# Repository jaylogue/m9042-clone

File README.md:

# M9042 Clone

M9042 clone is a PCB clone of the DEC M9042 Unibus module.  It provides an easy to build replacement for the original hardware, which is now hard to come by.

The original M9042 is a Unibus extension card for use in DEC PDP and Vax computers.  The M9042 makes it possible to extend a single Unibus bus across multiple chassis.  M9042s are used in pairs, one in each chassis, and connected via a set of three 40-pin ribbon cables (referred to as H854 cables).  The M9042 itself a short-form, dual height Unibus card which is designed to plug into the A and B connectors in a standard Unibus in/out slot.

The M9042 clone board is a straightforward redesign of the original M9042.  It has the same form-factor as the original and carries all the same Unibus signals and ground lines, in their same connector positions.  It also has a similar (although not identical) trace layout, with significant ground plane coverage, like the original.

* [M9042 clone schematic](docs/m9042-clone-sch.pdf)
* [M9042 clone PCB](docs/m9042-clone-pcb.pdf)

Documentation for the original M9042 (really just the board layout) can be found in the DW720 Field Maintenance Print Set, pp. 151-153 (available on [bitsavers](https://www.google.com/url?sa=t&rct=j&q=&esrc=s&source=web&cd=&cad=rja&uact=8&ved=2ahUKEwjrjoDqwcLzAhX1JTQIHfo5BsIQFnoECAIQAQ&url=http%3A%2F%2Fwww.bitsavers.org%2Fpdf%2Fdec%2Fvax%2F780%2FMP00497_DW780_Dec77.pdf&usg=AOvVaw0sKogK5xX24SyNcEcva4TK)).

The Computer History Wiki also has a useful page on the [H854 header pinout](https://gunkies.org/wiki/UNIBUS_H854_header_pinout).

## Repo Contents

The m9042-clone repo includes the following files:

* `kicad/*` – KiCad 5.x project files containing the schematic and PCB layout
* `pcb-plots/*` – Gerber and drill list files for the m9042-clone PCB
* `docs/*` – Various documentation files

## Parts List

A M9042 clone board is made up of exactly 4 parts: the PCB and three 40-pin latching ribbon cable headers. (Remember, though, that you need two M9042s to form an interconnect).  

I designed the board around the following headers.  These are intended to accommodate IDC ribbon cable connectors **without** strain reliefs.  Other choices (and sources) will likely work as well.

[TE Connectivity 5499913-9 – AMP-LATCH 40 Position Header](https://www.te.com/usa-en/product-5499913-9.html)

Three 40-pin ribbon cables are required to connect the boards together.  These are standard straight-through ribbon cables with 40-pin IDC connectors.  For ease of fitting the cables, its best if the cable exits the connector on the side with the registration tab.

## Ordering PCBs

The `pcb-plots` directory contains all the files necessary to order PCBs from a prototype PCB house such as [JLCPCB](https://jlcpcb.com/).

When ordering PCBs, be sure to request the following options:

* ENIG or hard gold surface finish
* Beveled connector edges
* Board thickness 1.4mm to 1.6mm

Board thicknesses of 1.6mm are common.  DEC specified its boards to be .056" (+/-0.005) thick, which makes 1.6mm a little big.  In practice, though, it does work.

Technically, a hard gold surface finish is best to ensure durability of the edge connectors against repeated insertions/removals.  Unfortunately it is expensive and not offered by many PCB manufactures.  ENIG is a more affordable compromise.

## M9042 Pin Numbering and Cable Orientation

One slight difference between the original M9042 and the clone is the numbering scheme used for the ribbon cable connectors.  Modern ribbon cable connectors place pin #1 in the upper right when looking into the connector pins with the registration slot facing up.  (A little arrow on the header marks the location of pin #1).  This orientation results in the red stripe on a ribbon cable being towards the right of the header when connected.

Historically, however, DEC considered the first pin (pin A) to be the one on the lower left of the connector, with numbering going in the opposite direction.  **In practice, this difference is of no consequence**, because all connections between pairs of M9042s are straight-though, and the registration tabs prevents connectors from being inserted upside-down.

Do however make sure to properly interconnect the three cables between their respective headers on each M9042 (J1-to-J1, J2-to-J2, etc.), as mixing these up would almost certainly be bad.

## WARNING

The M9042 clone has been successfully tested as an interconnect between a PDP-11/05 and an ME11-L box. _**This, however, is the extent of the testing done to date**_ (because that's all the hardware I have).

Because of this, anyone attempting to use the M9042 clone in their own equipment should proceed with caution, as I make no guarantee that it won't cause damage to your precious retro equipment.

If it does end up working for you, please drop me a line and let me know.

## License

The M9042 clone project, including the schematics, PCB layouts, all associated documentation and this README, are licensed under a [Creative Commons Attribution 4.0 International License](https://creativecommons.org/licenses/by/4.0/).  The file `LICENSE.TXT` contains a copy these provisions.

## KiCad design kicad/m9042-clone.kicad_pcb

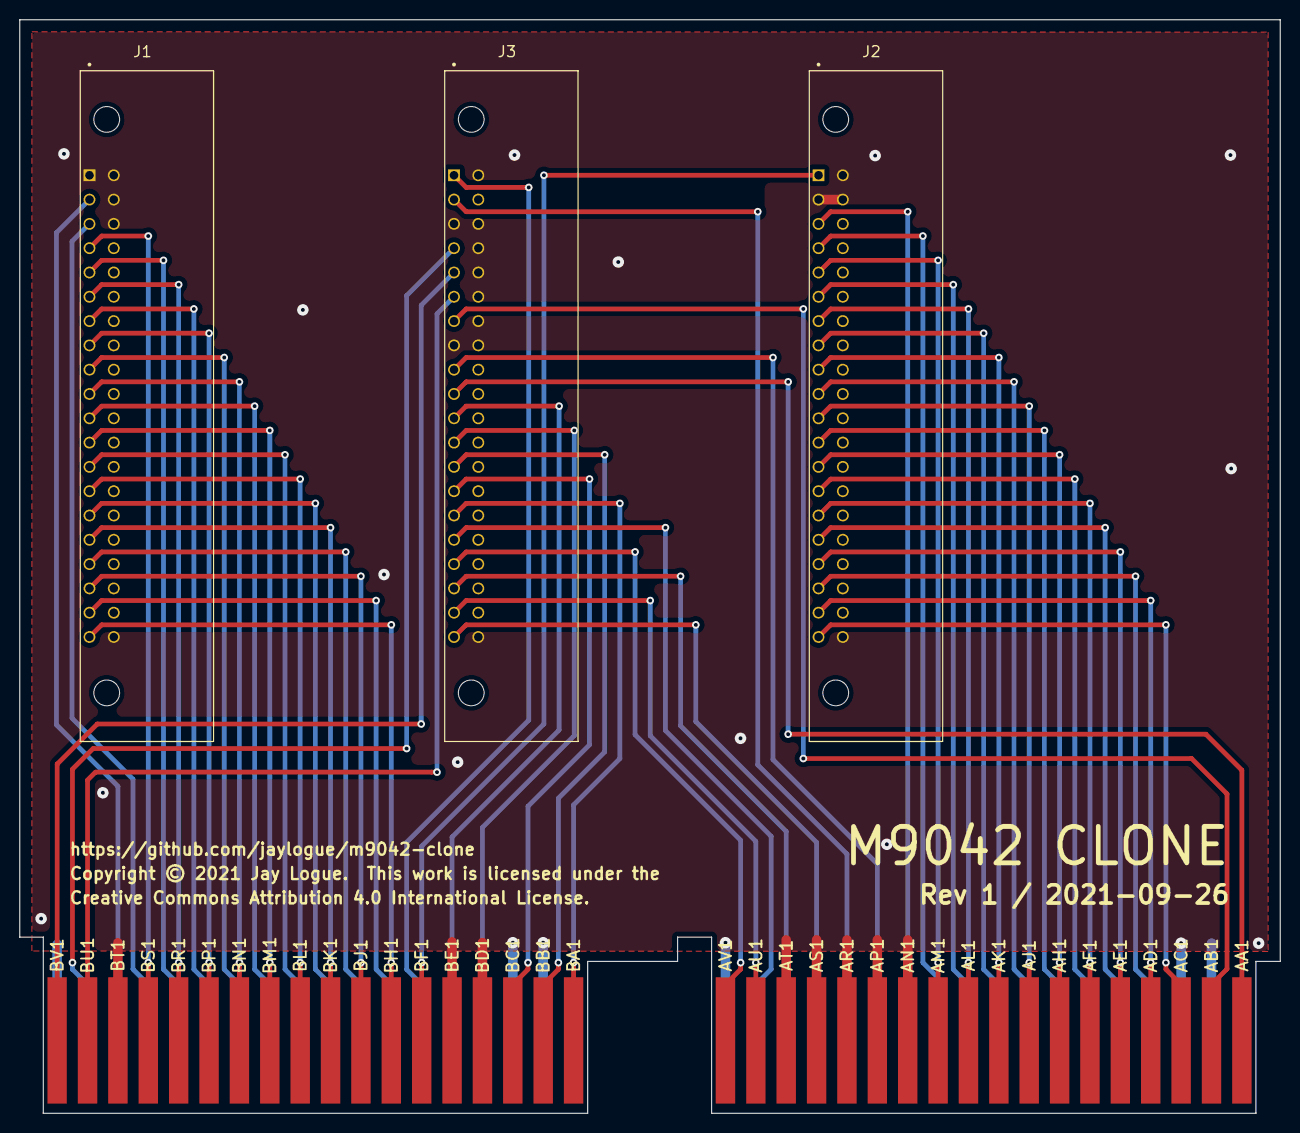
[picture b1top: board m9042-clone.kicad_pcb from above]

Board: 2 copper layers, 131.7 x 114.3 mm, 4 parts (0 on the bottom side), 57 nets.

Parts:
C1: CONN-DEC-DOUBLE-HEIGHT
J1, J2, J3: DEC-BERG-40; TE_5499786-9

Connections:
/A00: C1.BH2, J1.37
/A01: C1.BH1, J1.39
/A02: C1.BJ2, J1.33
/A03: C1.BJ1, J1.35
/A04: C1.BK2, J1.29
/A05: C1.BK1, J1.31
/A06: C1.BL2, J1.25
/A07: C1.BL1, J1.27
/A08: C1.BM2, J1.21
/A09: C1.BM1, J1.23
/A10: C1.BN2, J1.17
/A11: C1.BN1, J1.19
/A12: C1.BP2, J1.13
/A13: C1.BP1, J1.15
/A14: C1.BR2, J1.9
/A15: C1.BR1, J1.11
/A16: C1.BS2, J1.5
/A17: C1.BS1, J1.7
/AC_LO: C1.BF1, J2.1
/BBSY: C1.AP2, J3.17
/BG4: C1.BE2, J3.21
/BG5: C1.BB1, J3.25
/BG6: C1.BA1, J3.29
/BG7: C1.AV1, J3.33
/BR4: C1.BD2, J3.23
/BR5: C1.BC1, J3.27
/BR6: C1.AU2, J3.31
/BR7: C1.AT2, J3.35
/C0: C1.BU2, J3.7
/C1: C1.BT2, J1.3
/D00: C1.AC1, J2.39
/D01: C1.AD2, J2.35
/D02: C1.AD1, J2.37
/D03: C1.AE2, J2.31
/D04: C1.AE1, J2.33
/D05: C1.AF2, J2.27
/D06: C1.AF1, J2.29
/D07: C1.AH2, J2.23
/D08: C1.AH1, J2.25
/D09: C1.AJ2, J2.19
/D10: C1.AJ1, J2.21
/D11: C1.AK2, J2.15
/D12: C1.AK1, J2.17
/D13: C1.AL2, J2.11
/D14: C1.AL1, J2.13
/D15: C1.AM2, J2.7
/DC_LO: C1.BF2, J3.1
/INIT: C1.AA1, J3.19
/INTR: C1.AB1, J3.13
/MSYN: C1.BV1, J3.9
/NPG: C1.AU1, J3.37
/NPR: C1.AS2, J3.39
/PA: C1.AM1, J2.9
/PB: C1.AN2, J2.5
/SACK: C1.AR2, J3.3
/SSYN: C1.BU1, J3.11
GND: C1.AB2, C1.AC2, C1.AN1, C1.AP1, C1.AR1, C1.AS1, C1.AT1, C1.AV2, C1.BB2, C1.BC2, C1.BD1, C1.BE1, C1.BT1, C1.BV2, J1.1, J1.2, J1.4, J1.6, J1.8, J1.10, J1.12, J1.14, J1.16, J1.18, J1.20, J1.22, J1.24, J1.26, J1.28, J1.30, J1.32, J1.34, J1.36, J1.38, J1.40, J2.2, J2.3, J2.4, J2.6, J2.8, J2.10, J2.12, J2.14, J2.16, J2.18, J2.20, J2.22, J2.24, J2.26, J2.28, J2.30, J2.32, J2.34, J2.36, J2.38, J2.40, J3.2, J3.4, J3.5, J3.6, J3.8, J3.10, J3.12, J3.14, J3.15, J3.16, J3.18, J3.20, J3.22, J3.24, J3.26, J3.28, J3.30, J3.32, J3.34, J3.36, J3.38, J3.40

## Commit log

2021-10-11 Revision 1

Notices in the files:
kicad/m9042-clone.kicad_pcb:
Copyright © 2021 Jay Logue.  This work is licensed under the
